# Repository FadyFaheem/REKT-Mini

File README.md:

# REKT-Mini
Built an embedded sensor data acquisition system with custom firmware (ATTiny85) and Python data processing pipeline, implementing real-time sensor fusion and calibration algorithms that reduced measurement time by ~85% compared to manual methods across 4+ validation runs.

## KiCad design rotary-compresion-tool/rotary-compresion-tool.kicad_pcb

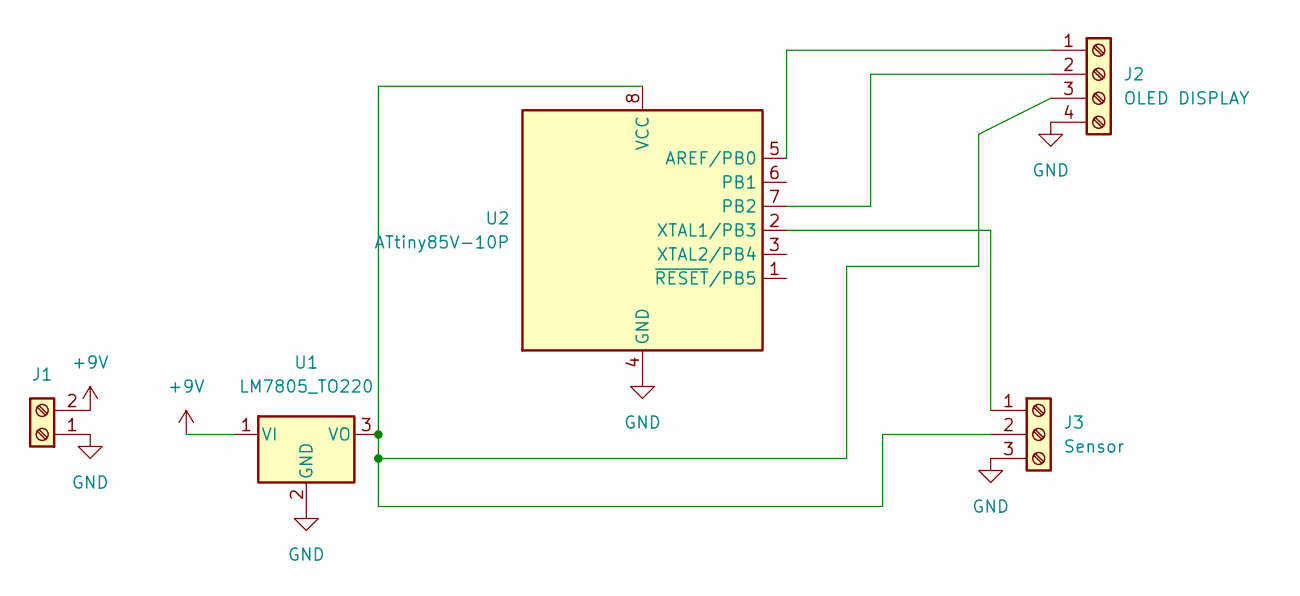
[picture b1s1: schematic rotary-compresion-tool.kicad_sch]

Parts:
J1: TerminalBlock_bornier-2_P5.08mm
J2: OLED DISPLAY; FanPinHeader_1x04_P2.54mm_Vertical
J3: Sensor; TerminalBlock_bornier-3_P5.08mm
U1: LM7805_TO220; TO-220-3_Vertical
U2: ATtiny85V-10P; DIP-8_W7.62mm

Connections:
+9V: J1.2, U1.1 (VI)
GND: J1.1, J2.4, J3.3, U1.2 (GND), U2.4 (GND)
unnamed: J2.1, U2.5 (AREF/PB0)
unnamed: J2.2, U2.7 (PB2)
unnamed: J2.3, J3.2, U1.3 (VO), U2.8 (VCC)
unnamed: J3.1, U2.2 (XTAL1/PB3)

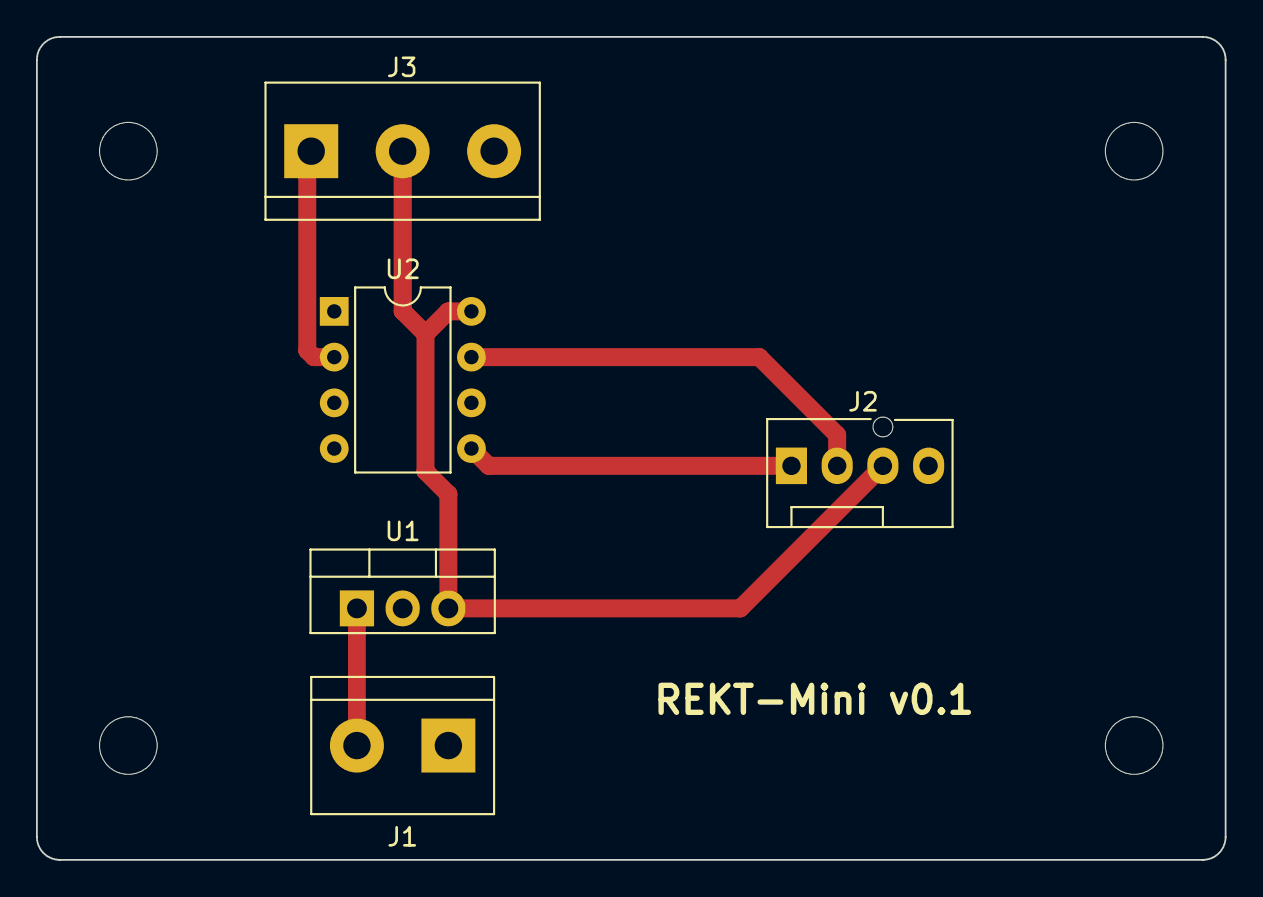
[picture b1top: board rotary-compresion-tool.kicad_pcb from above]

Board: 2 copper layers, 66.0 x 45.7 mm, 5 parts (0 on the bottom side), 6 nets.

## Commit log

2022-11-02 Geber and schm
2022-11-04 license
2022-11-04 Update LICENSE
2022-11-05 Original Code
2022-11-18 Finished Attiny85 Code
2026-01-03 Revise README description for clarity and detail
